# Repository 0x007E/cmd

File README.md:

# `CMD` - Color Matrix Display

The `CMD` is a board with a matrix of [APA102](#additional-information) or any other `SPI` controllable `RGB-LED`. The board itself can be driven with a voltage from `3V3-5V` and controlled over the [APA102 driver library](https://github.com/0x007E/drivers-led-apa102).

| Experience  | Level                                                                               |
|:------------|:-----------------------------------------------------------------------------------:|
| Soldering   |  |

# Downloads

| Type      | File                                                                                                                                                 | Description     |
|:---------:|:----------------------------------------------------------------------------------------------------------------------------------------------------:|:----------------|
| Schematic | [pdf](https://github.com/0x007E/cmd/releases/latest/download/schematic.pdf) / [cadlab](https://cadlab.io/project/30127/main/files)                   | Schematic files |
| Board     | [pdf](https://github.com/0x007E/cmd/releases/latest/download/pcb.pdf) / [cadlab](https://cadlab.io/project/30127/main/files)                         | Board file      |
| Drill     | [pdf](https://github.com/0x007E/cmd/releases/latest/download/drill.pdf)                                                                              | Drill file      |
| PCB       | [zip](https://github.com/0x007E/cmd/releases/latest/download/kicad.zip) / [tar](https://github.com/0x007E/cmd/releases/latest/download/kicad.tar.gz) | KiCAD/Gerber/BoM/Drill files |
| Mechanical | [zip](https://github.com/0x007E/cmd/releases/latest/download/freecad.zip) / [tar](https://github.com/0x007E/cmd/releases/latest/download/freecad.tar.gz) | FreeCAD/Housing and exported step/stl files |

# Hardware

The pcb is created with `KiCAD`, the housing with `FreeCAD`. All files are built with `github actions` so that they are ready for a production environment.

## PCB

The circuit board is populated on both sides (Top, Bottom). The best way for soldering the `SMD` components is within a vapor phase soldering system and for the `THT` components with a standard soldering system.

### Top Layer

### Bottom Layer

## Mechanical

The housing has a tolerance of `0.2mm` on each side of the case. So the pcb should fit perfectly in the housing. The tolerance can be modified with `FreeCAD` in the `Parameter` Spreadsheet.

### Assembled

### Exploded

# Additional Information

| Type       | Link                                                                                                      | Description                                        |
|:----------:|:---------------------------------------------------------------------------------------------------------:|:---------------------------------------------------|
| APA102     | [pdf](https://cdn.sparkfun.com/datasheets/Components/LED/APA102C.pdf)                                     | RGB Full Color LED                                 |
| T3A33BRG   | [pdf](https://mm.digikey.com/Volume0/opasdata/d220001/medias/docus/6794/3147_T3A33BRG-H9C0002X1U1930.pdf) | Harvatek Surface Mount PLCC IC+RGB LEDs Data Sheet |

---

R. GAECHTER

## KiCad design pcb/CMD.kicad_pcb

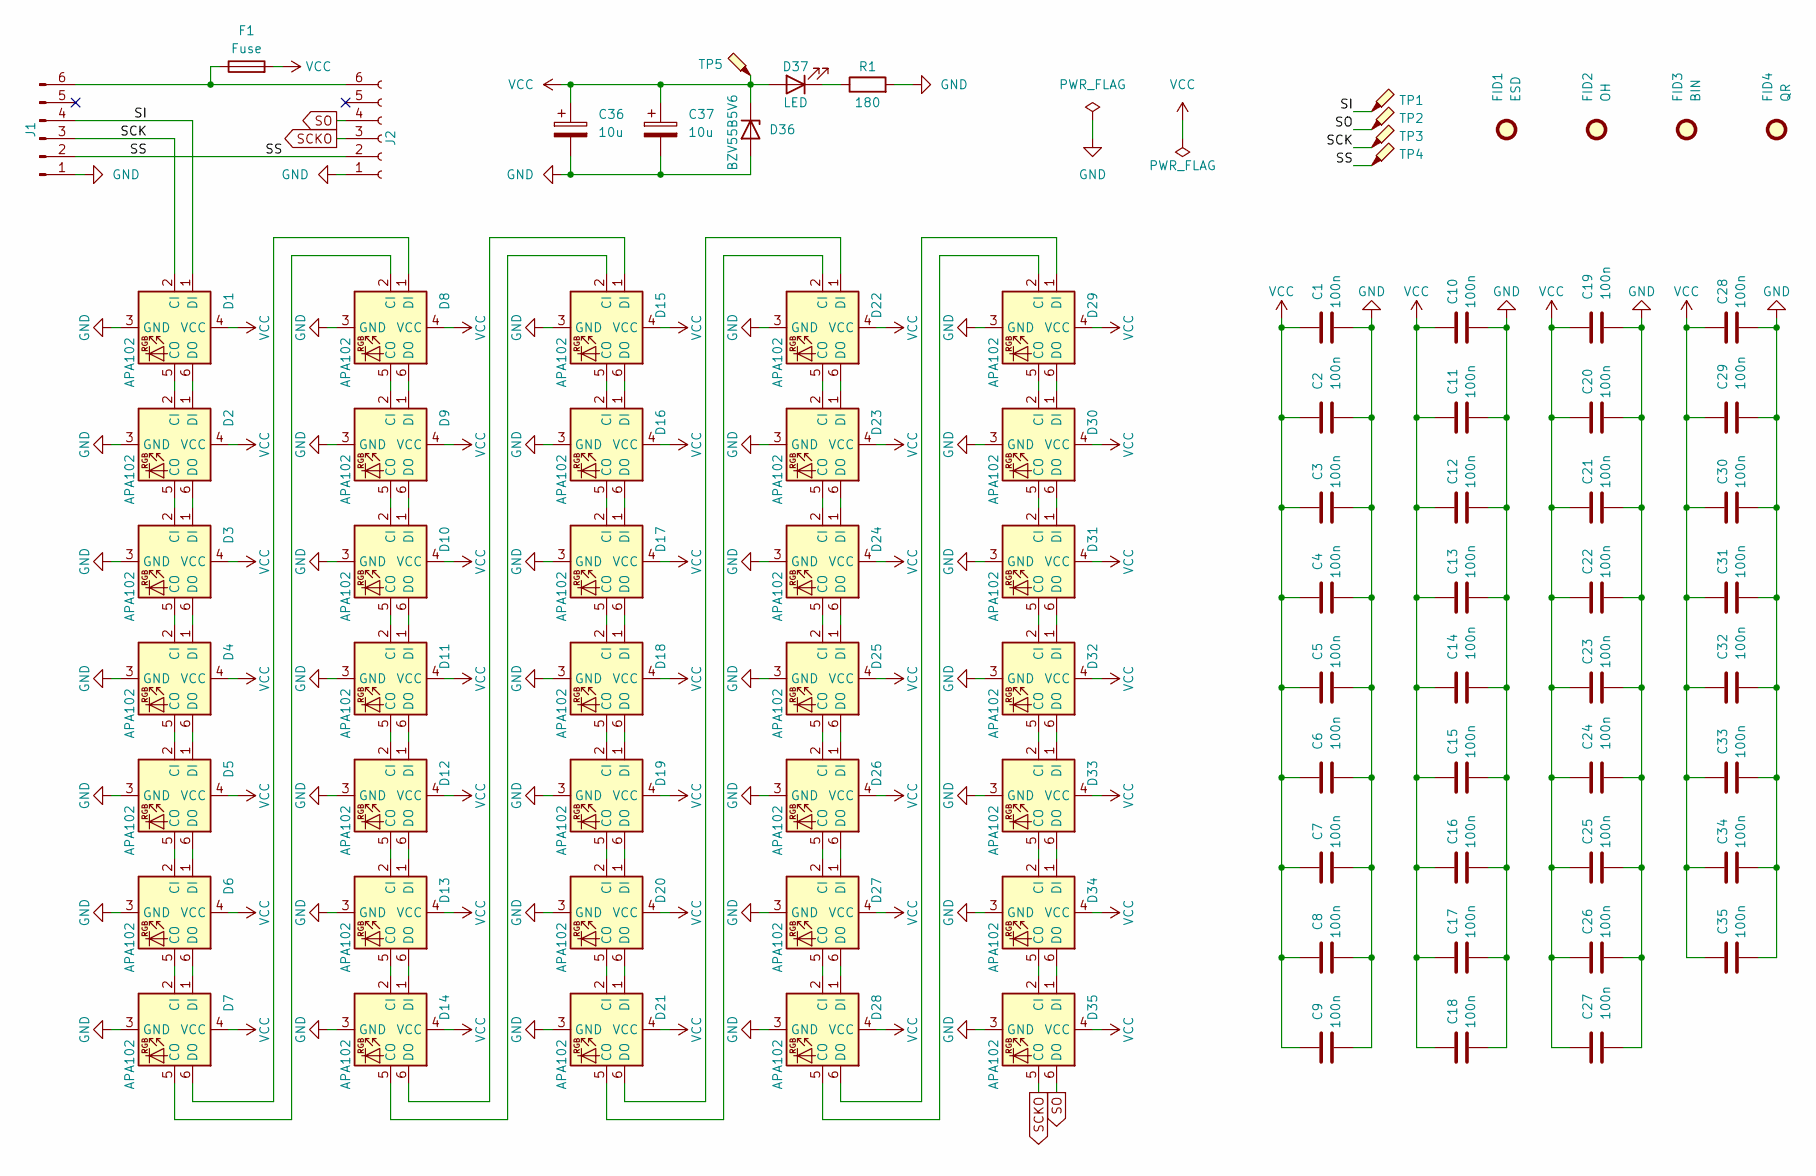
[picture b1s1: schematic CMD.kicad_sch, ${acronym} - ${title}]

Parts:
C1, C2, C3, C4, C5, C6, C7, C8, C9, C10, C11, C12, C13, C14, C15, C16, C17, C18, C19, C20, C21, C22, C23, C24, C25, C26, C27, C28, C29, C30, C31, C32, C33, C34, C35: 100n; C_1206_3216Metric
C36, C37: 10u; CP_EIA-6032-28_Kemet-C
D1, D2, D3, D4, D5, D6, D7, D8, D9, D10, D11, D12, D13, D14, D15, D16, D17, D18, D19, D20, D21, D22, D23, D24, D25, D26, D27, D28, D29, D30, D31, D32, D33, D34, D35: APA102; LED_RGB_5050-6
D36: BZV55B5V6; D_MiniMELF
D37: LED; LED_1206_3216Metric
F1: Fuse; Fuse_1206_3216Metric
FID1: ESD; ESD-Logo_6.6x6mm_SilkScreen
FID2: OH; OSHW-Logo_5.7x6mm_SilkScreen
FID3: BIN; WEEE-Logo_4.2x6mm_SilkScreen
FID4: QR; QR_0x007e_very_small
J1: Conn_01x06_Pin; HARWIN_M20-8890645_Pin_Header
J2: Conn_01x06_Socket; HARWIN_M20-7910642R_Pin_Socket
R1: 180; R_1206_3216Metric
TP1, TP2, TP3, TP4, TP5: TestPoint_Probe; TestPoint_Pad_D1.0mm

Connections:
/SCK: D1.2 (CI), J1.3, TP3.1
/SI: D1.1 (DI), J1.4, TP1.1
/SS: J1.2, J2.2, TP4.1
GND: C1.1, C2.2, C3.1, C4.1, C5.1, C6.2, C7.1, C8.1, C9.1, C10.1, C11.1, C12.1, C13.1, C14.2, C15.1, C16.1, C17.1, C18.1, C19.2, C20.1, C21.1, C22.1, C23.1, C24.2, C25.1, C26.1, C27.2, C28.1, C29.2, C30.1, C31.1, C32.2, C33.1, C34.1, C35.1, C36.2, C37.2, D1.3 (GND), D2.3 (GND), D3.3 (GND), D4.3 (GND), D5.3 (GND), D6.3 (GND), D7.3 (GND), D8.3 (GND), D9.3 (GND), D10.3 (GND), D11.3 (GND), D12.3 (GND), D13.3 (GND), D14.3 (GND), D15.3 (GND), D16.3 (GND), D17.3 (GND), D18.3 (GND), D19.3 (GND), D20.3 (GND), D21.3 (GND), D22.3 (GND), D23.3 (GND), D24.3 (GND), D25.3 (GND), D26.3 (GND), D27.3 (GND), D28.3 (GND), D29.3 (GND), D30.3 (GND), D31.3 (GND), D32.3 (GND), D33.3 (GND), D34.3 (GND), D35.3 (GND), D36.2 (A), J1.1, J2.1, R1.2
unnamed: D1.5 (CO), D2.2 (CI)
unnamed: D1.6 (DO), D2.1 (DI)
unnamed: D2.5 (CO), D3.2 (CI)
unnamed: D2.6 (DO), D3.1 (DI)
unnamed: D3.5 (CO), D4.2 (CI)
unnamed: D3.6 (DO), D4.1 (DI)
unnamed: D4.5 (CO), D5.2 (CI)
unnamed: D4.6 (DO), D5.1 (DI)
unnamed: D5.5 (CO), D6.2 (CI)
unnamed: D5.6 (DO), D6.1 (DI)
unnamed: D6.5 (CO), D7.2 (CI)
unnamed: D6.6 (DO), D7.1 (DI)
unnamed: D7.5 (CO), D8.2 (CI)
unnamed: D7.6 (DO), D8.1 (DI)
unnamed: D8.5 (CO), D9.2 (CI)
unnamed: D8.6 (DO), D9.1 (DI)
unnamed: D9.5 (CO), D10.2 (CI)
unnamed: D10.5 (CO), D11.2 (CI)
unnamed: D9.6 (DO), D10.1 (DI)
unnamed: D10.6 (DO), D11.1 (DI)
unnamed: D11.5 (CO), D12.2 (CI)
unnamed: D11.6 (DO), D12.1 (DI)
unnamed: D12.5 (CO), D13.2 (CI)
unnamed: D12.6 (DO), D13.1 (DI)
unnamed: D13.5 (CO), D14.2 (CI)
unnamed: D13.6 (DO), D14.1 (DI)
unnamed: D14.5 (CO), D15.2 (CI)
unnamed: D14.6 (DO), D15.1 (DI)
unnamed: D15.5 (CO), D16.2 (CI)
unnamed: D15.6 (DO), D16.1 (DI)
unnamed: D16.5 (CO), D17.2 (CI)
unnamed: D16.6 (DO), D17.1 (DI)
unnamed: D17.5 (CO), D18.2 (CI)
unnamed: D17.6 (DO), D18.1 (DI)
unnamed: D18.5 (CO), D19.2 (CI)
unnamed: D18.6 (DO), D19.1 (DI)
unnamed: D19.5 (CO), D20.2 (CI)
unnamed: D19.6 (DO), D20.1 (DI)
unnamed: D20.5 (CO), D21.2 (CI)
unnamed: D20.6 (DO), D21.1 (DI)
unnamed: D21.5 (CO), D22.2 (CI)
unnamed: D21.6 (DO), D22.1 (DI)
unnamed: D22.5 (CO), D23.2 (CI)
unnamed: D22.6 (DO), D23.1 (DI)
unnamed: D23.5 (CO), D24.2 (CI)
unnamed: D23.6 (DO), D24.1 (DI)
unnamed: D24.5 (CO), D25.2 (CI)
unnamed: D24.6 (DO), D25.1 (DI)
unnamed: D25.5 (CO), D26.2 (CI)
unnamed: D25.6 (DO), D26.1 (DI)
unnamed: D26.5 (CO), D27.2 (CI)
unnamed: D26.6 (DO), D27.1 (DI)
unnamed: D27.5 (CO), D28.2 (CI)
unnamed: D27.6 (DO), D28.1 (DI)
unnamed: D28.5 (CO), D29.2 (CI)
unnamed: D28.6 (DO), D29.1 (DI)
unnamed: D29.5 (CO), D30.2 (CI)
unnamed: D29.6 (DO), D30.1 (DI)
unnamed: D30.5 (CO), D31.2 (CI)
unnamed: D30.6 (DO), D31.1 (DI)
unnamed: D31.5 (CO), D32.2 (CI)
unnamed: D31.6 (DO), D32.1 (DI)
unnamed: D32.5 (CO), D33.2 (CI)
unnamed: D32.6 (DO), D33.1 (DI)
unnamed: D33.5 (CO), D34.2 (CI)
unnamed: D33.6 (DO), D34.1 (DI)
unnamed: D34.5 (CO), D35.2 (CI)
unnamed: D34.6 (DO), D35.1 (DI)
unnamed: D37.1 (K), R1.1
unnamed: F1.1, J1.6, J2.6
SCKO: D35.5 (CO), J2.3
SO: D35.6 (DO), J2.4, TP2.1
VCC: C1.2, C2.1, C3.2, C4.2, C5.2, C6.1, C7.2, C8.2, C9.2, C10.2, C11.2, C12.2, C13.2, C14.1, C15.2, C16.2, C17.2, C18.2, C19.1, C20.2, C21.2, C22.2, C23.2, C24.1, C25.2, C26.2, C27.1, C28.2, C29.1, C30.2, C31.2, C32.1, C33.2, C34.2, C35.2, C36.1, C37.1, D1.4 (VCC), D2.4 (VCC), D3.4 (VCC), D4.4 (VCC), D5.4 (VCC), D6.4 (VCC), D7.4 (VCC), D8.4 (VCC), D9.4 (VCC), D10.4 (VCC), D11.4 (VCC), D12.4 (VCC), D13.4 (VCC), D14.4 (VCC), D15.4 (VCC), D16.4 (VCC), D17.4 (VCC), D18.4 (VCC), D19.4 (VCC), D20.4 (VCC), D21.4 (VCC), D22.4 (VCC), D23.4 (VCC), D24.4 (VCC), D25.4 (VCC), D26.4 (VCC), D27.4 (VCC), D28.4 (VCC), D29.4 (VCC), D30.4 (VCC), D31.4 (VCC), D32.4 (VCC), D33.4 (VCC), D34.4 (VCC), D35.4 (VCC), D36.1 (K), D37.2 (A), F1.2, TP5.1

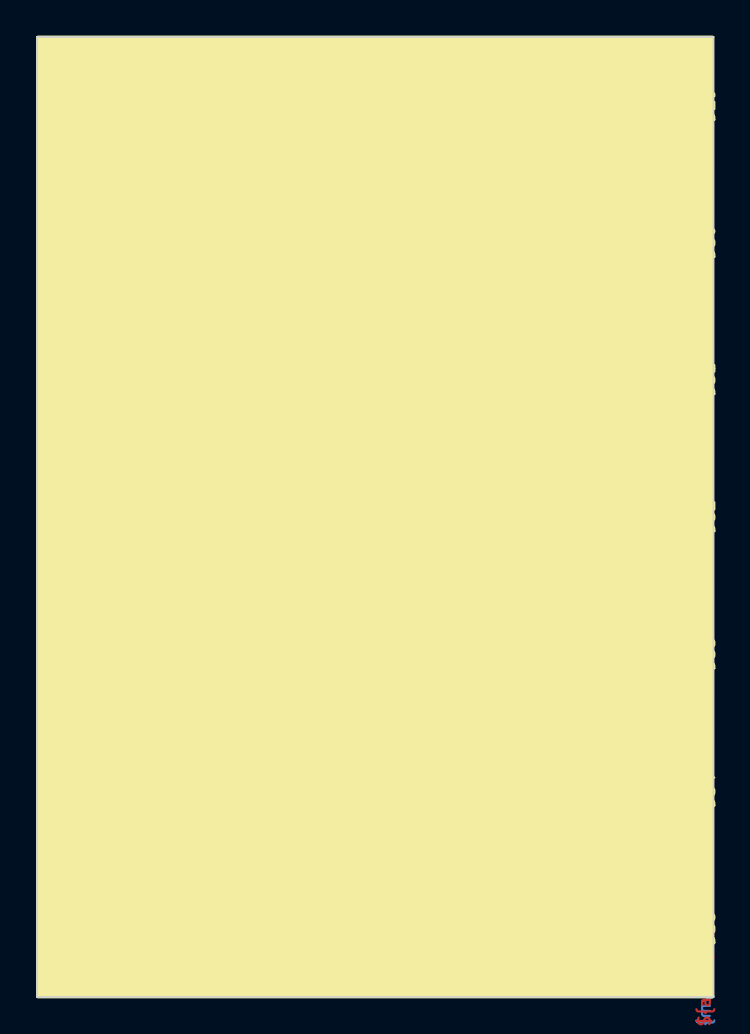
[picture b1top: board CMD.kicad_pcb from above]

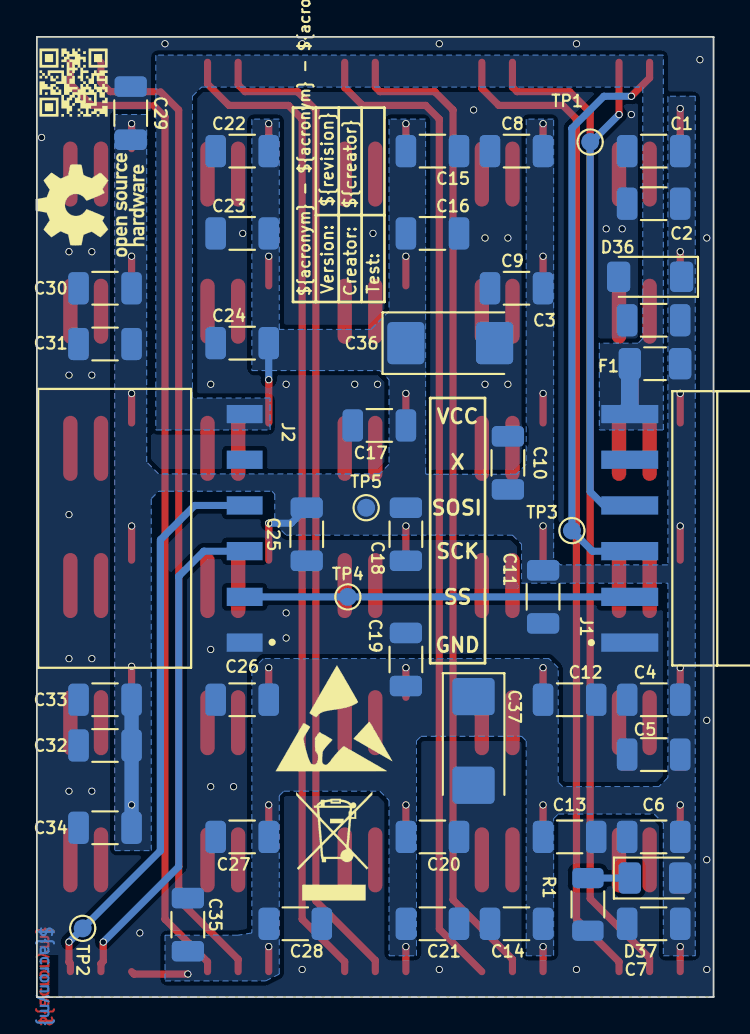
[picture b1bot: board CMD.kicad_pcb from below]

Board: 2 copper layers, 37.6 x 53.3 mm, 87 parts (52 on the bottom side), 77 nets.

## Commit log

2026-03-03 Add pcb layout
2026-03-03 Add README.md
2026-03-03 Add build pipeline
2026-03-03 Add release pipeline
2026-03-09 Remove invalid text
2026-04-08 Arrange fabrication layers
2026-04-08 Add reference designator to fabrication layer
2026-04-08 Add fabrication identifier
2026-04-08 Remove led values from fabrication layer
2026-04-13 Fix led position and add extended dimensioning
2026-04-13 Add mechanical parts
2026-04-14 Lower pcb width
2026-04-14 Shrink housing width
2026-04-22 Adapt vendor(id)
2026-05-13 Add assembly explosion
2026-05-13 Extend README.md

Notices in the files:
README.md:
License CC By-NC-SA
parts and their libraries:
license: CC BY-NC-SA 4.0
